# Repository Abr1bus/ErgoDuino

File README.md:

# Ergoduino, an ergo/mech/DIY keyboard

## The project

ErgoDuino is a mechanical keyboard project designed by [Abr1bu5](https://github.com/Abr1bus).

I started to think about it during the first Covid's quarantime, when I was losing my time on [r/MechanicalKeyboard](https://reddit.com/r/MechanicalKeyboards)...

## The tools I used (or will use)

* Layout : [Keyboard Layout Editor](http://www.keyboard-layout-editor.com/)
* Plate : [Plate and Case Builder](http://builder.swillkb.com/)
* Schematics and PCB : [KiCAD](https://kicad.org/)
* Keyboard firmware : [QMK](https://qmk.fm/)

## Where I found all my inspiration/knowledge

* [r/MechanicalKeyboards](https://reddit.com/r/MechanicalKeyboards)
* [r/olkb](https://www.reddit.com/r/olkb/)
* [r/CustomKeyboards](https://www.reddit.com/r/CustomKeyboards/)
* [@Help-14](https://github.com/help-14/mechanical-keyboard) on Github

# Releases

My very first version is on the repo (dev branch), but I don't know if it's working, so if you want to make it, you should check everything !

## Contributing

1. Fork it (<https://github.com/Abr1bus/ErgoDuino>)
2. Create your feature branch `git checkout -b feature/fooBar`
3. Commit your changes `git commit -am 'Add some fooBar'`
4. Push to the branch `git push origin feature/fooBar`
5. Create a new Pull Request

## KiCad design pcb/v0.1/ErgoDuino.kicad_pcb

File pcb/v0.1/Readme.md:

# My KiCAD project

----

Here you will found my KiCAD project, but I have not yet include my libraries.

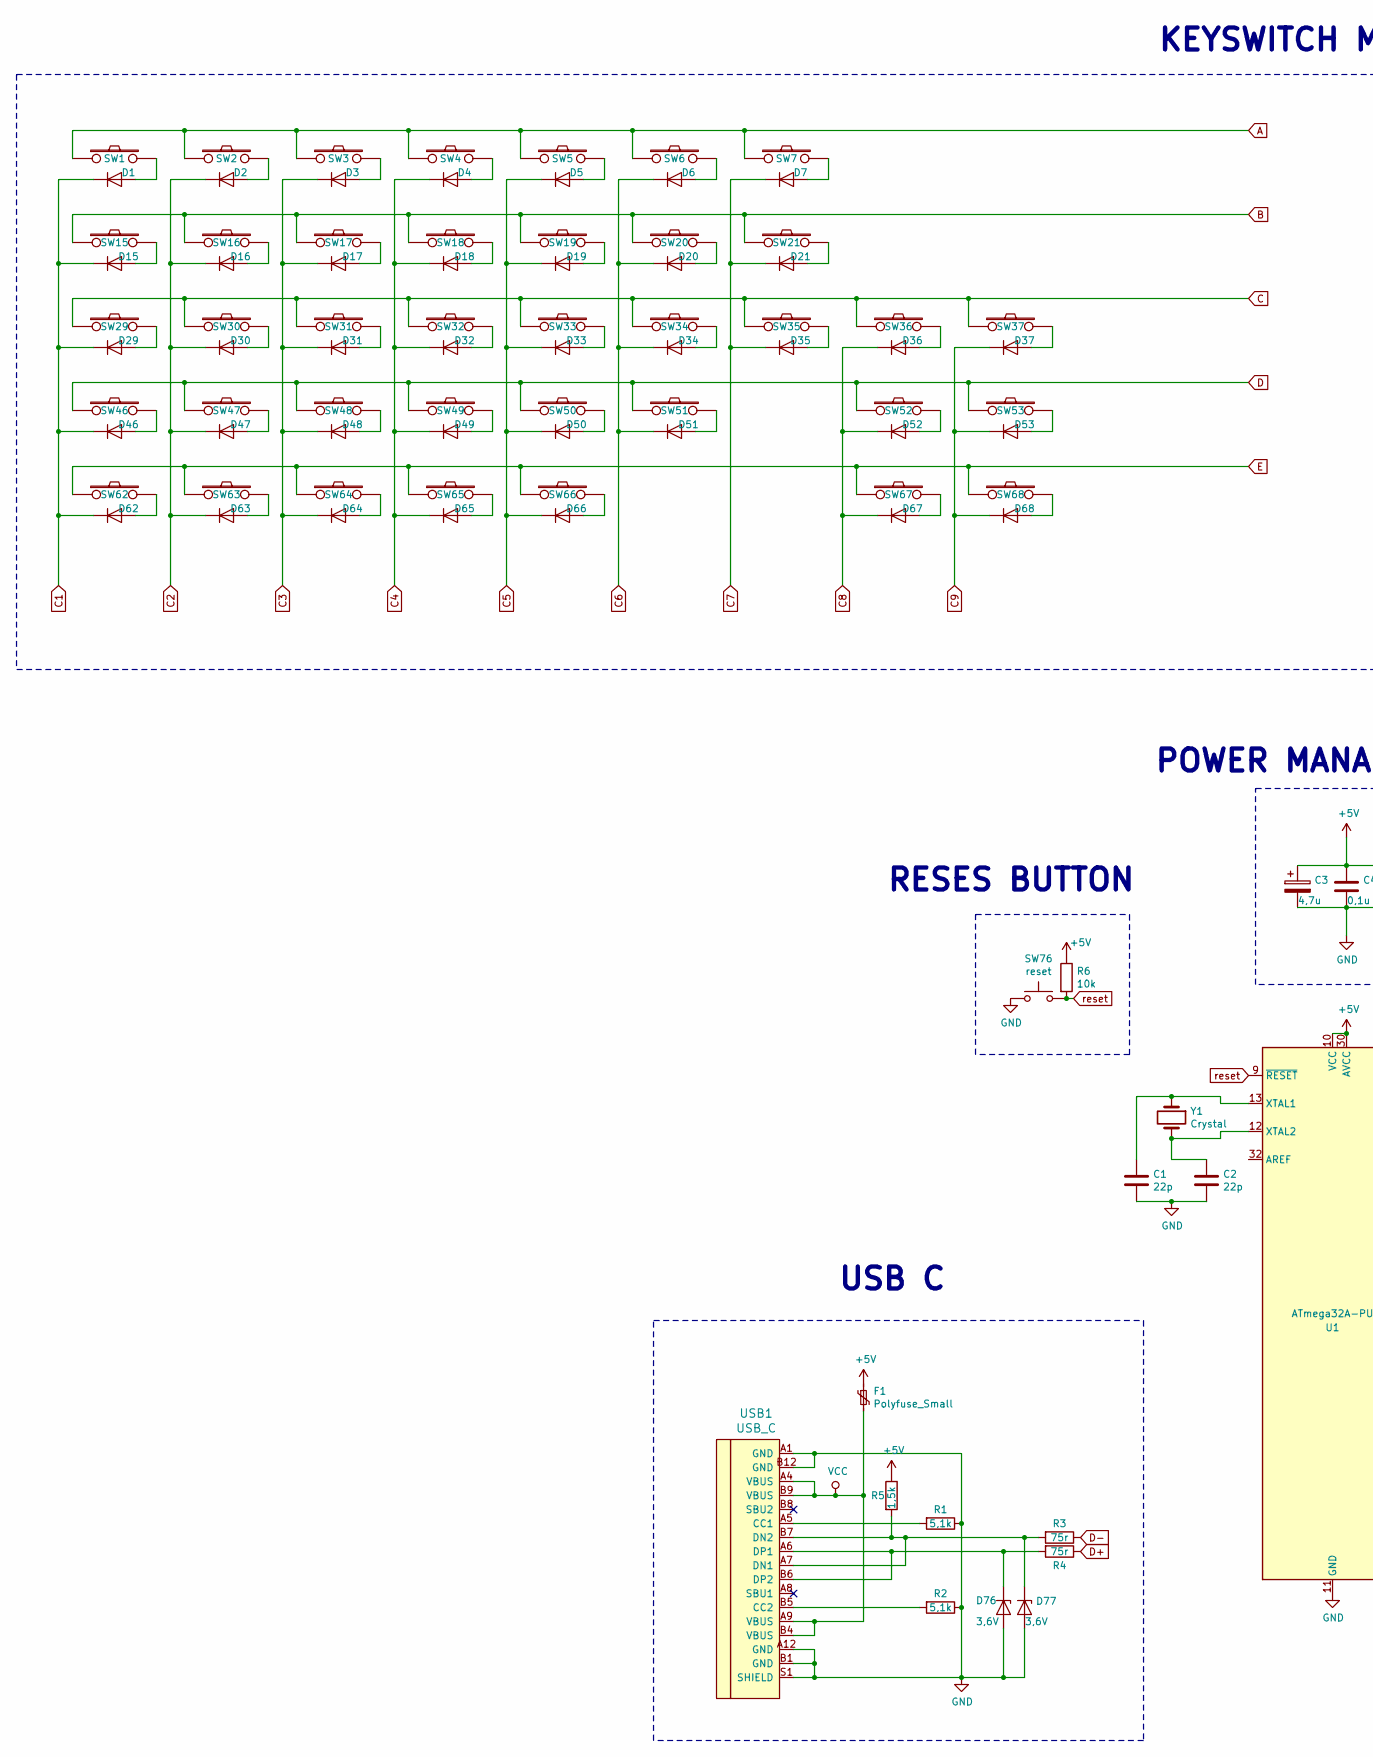
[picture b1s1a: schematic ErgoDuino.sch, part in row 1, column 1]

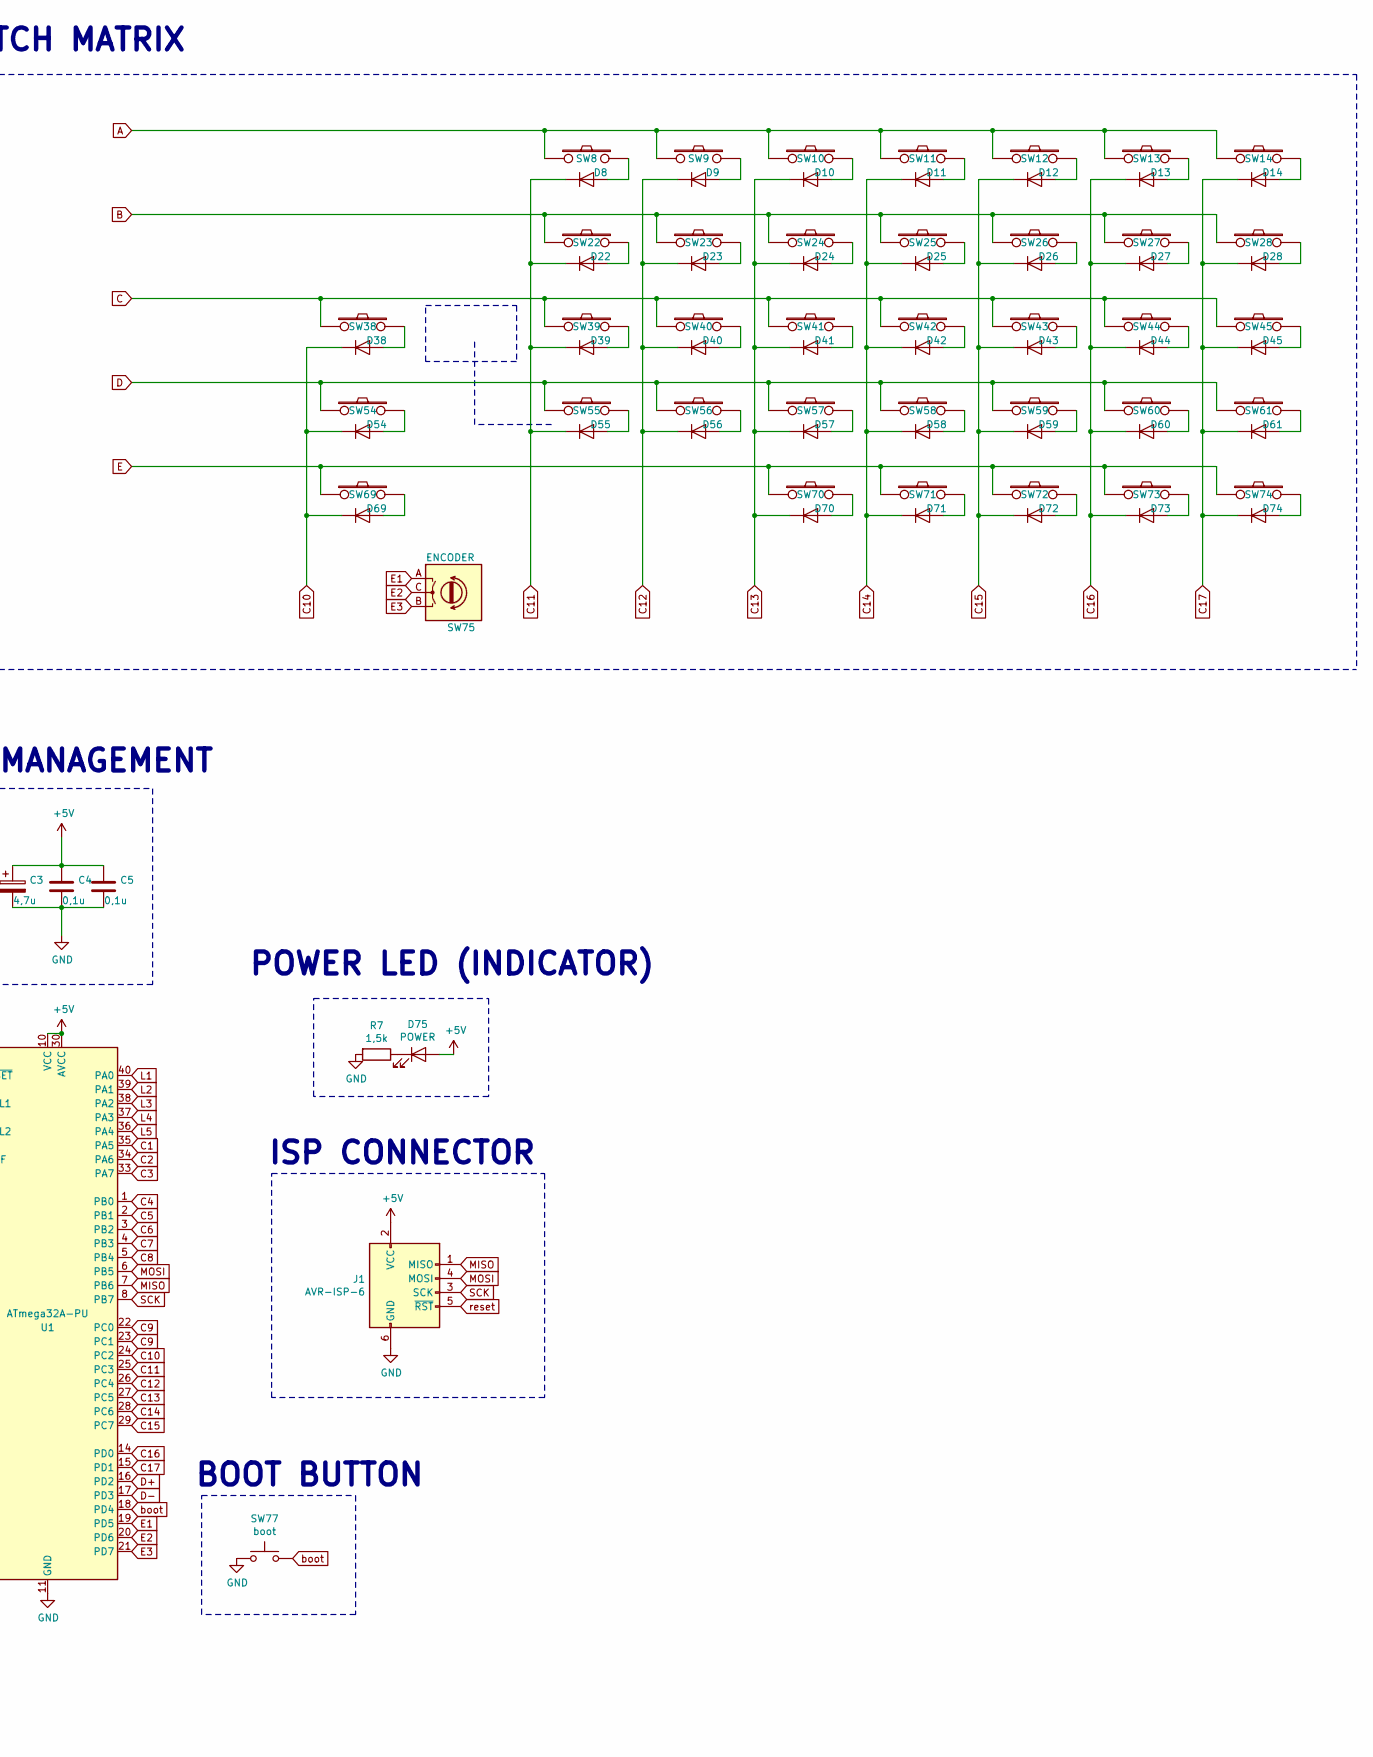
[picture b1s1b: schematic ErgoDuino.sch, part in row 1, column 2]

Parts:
C1, C2: 22p; CP_Radial_D4.0mm_P1.50mm
C3: 4,7u; CP_Radial_D4.0mm_P1.50mm
C4, C5: 0,1u; CP_Radial_D4.0mm_P1.50mm
D1, D2, D3, D4, D5, D6, D7, D8, D9, D10, D11, D12, D13, D14, D15, D16, D17, D18, D19, D20, D21, D22, D23, D24, D25, D26, D27, D28, D29, D30, D31, D32, D33, D34, D35, D36, D37, D38, D39, D40, D41, D42, D43, D44, D45, D46, D47, D48, D49, D50, D51, D52, D53, D54, D55, D56, D57, D58, D59, D60, D61, D62, D63, D64, D65, D66, D67, D68, D69, D70, D71, D72, D73, D74: D; DIODE
D75: POWER; LED_3MM
D76, D77: 3,6V; DIODE
F1: Polyfuse_Small; polyfuse_5.1mm
J1: AVR-ISP-6; AVR_ICSP_3x2
R1, R2: 5,1k; R_Axial_DIN0204_L3.6mm_D1.6mm_P5.08mm_Horizontal
R3, R4: 75r; R_Axial_DIN0204_L3.6mm_D1.6mm_P5.08mm_Horizontal
R5, R7: 1,5k; R_Axial_DIN0204_L3.6mm_D1.6mm_P5.08mm_Horizontal
R6: 10k; R_Axial_DIN0204_L3.6mm_D1.6mm_P5.08mm_Horizontal
SW1, SW14, SW15, SW21, SW22, SW28, SW29, SW35, SW39, SW45, SW46, SW61: SWITCH_PUSH; SW_Cherry_MX_1.50u_PCB
SW2, SW3, SW4, SW5, SW6, SW7, SW8, SW9, SW10, SW11, SW12, SW13, SW16, SW17, SW18, SW19, SW20, SW23, SW24, SW25, SW26, SW27, SW30, SW31, SW32, SW33, SW34, SW36, SW37, SW38, SW40, SW41, SW42, SW43, SW44, SW47, SW48, SW49, SW50, SW51, SW53, SW54, SW55, SW56, SW57, SW58, SW59, SW60, SW62, SW63, SW64, SW65, SW66, SW68, SW69, SW70, SW71, SW72, SW73, SW74: SWITCH_PUSH; SW_Cherry_MX_1.00u_PCB
SW52, SW67: SWITCH_PUSH; SW_Cherry_MX_2.00u_PCB
SW75: ENCODER; RotaryEncoder_Alps_EC11E-Switch_Vertical_H20mm
SW76: reset; SW_PUSH_6mm
SW77: boot; SW_PUSH_6mm
U1: ATmega32A-PU; DIP-40_W15.24mm
USB1: USB_C; USB_C_GCT_USB4085
Y1: Crystal; Crystal_HC49-4H_Vertical

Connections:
+5V: C3.1, C4.1, C5.1, D75.2 (A), F1.1, J1.2 (VCC), R5.1, R6.1, U1.10 (VCC), U1.30 (AVCC)
A: SW1.1, SW2.1, SW3.1, SW4.1, SW5.1, SW6.1, SW7.1, SW8.1, SW9.1, SW10.1, SW11.1, SW12.1, SW13.1, SW14.1
B: SW15.1, SW16.1, SW17.1, SW18.1, SW19.1, SW20.1, SW21.1, SW22.1, SW23.1, SW24.1, SW25.1, SW26.1, SW27.1, SW28.1
C: SW29.1, SW30.1, SW31.1, SW32.1, SW33.1, SW34.1, SW35.1, SW36.1, SW37.1, SW38.1, SW39.1, SW40.1, SW41.1, SW42.1, SW43.1, SW44.1, SW45.1
C1: D1.1 (K), D15.1 (K), D29.1 (K), D46.1 (K), D62.1 (K), U1.35 (PA5)
C2: D2.1 (K), D16.1 (K), D30.1 (K), D47.1 (K), D63.1 (K), U1.34 (PA6)
C3: D3.1 (K), D17.1 (K), D31.1 (K), D48.1 (K), D64.1 (K), U1.33 (PA7)
C4: D4.1 (K), D18.1 (K), D32.1 (K), D49.1 (K), D65.1 (K), U1.1 (PB0)
C5: D5.1 (K), D19.1 (K), D33.1 (K), D50.1 (K), D66.1 (K), U1.2 (PB1)
C6: D6.1 (K), D20.1 (K), D34.1 (K), D51.1 (K), U1.3 (PB2)
C7: D7.1 (K), D21.1 (K), D35.1 (K), U1.4 (PB3)
C8: D36.1 (K), D52.1 (K), D67.1 (K), U1.5 (PB4)
C9: D37.1 (K), D53.1 (K), D68.1 (K), U1.22 (PC0), U1.23 (PC1)
C10: D38.1 (K), D54.1 (K), D69.1 (K), U1.24 (PC2)
C11: D8.1 (K), D22.1 (K), D39.1 (K), D55.1 (K), U1.25 (PC3)
C12: D9.1 (K), D23.1 (K), D40.1 (K), D56.1 (K), U1.26 (PC4)
C13: D10.1 (K), D24.1 (K), D41.1 (K), D57.1 (K), D70.1 (K), U1.27 (PC5)
C14: D11.1 (K), D25.1 (K), D42.1 (K), D58.1 (K), D71.1 (K), U1.28 (PC6)
C15: D12.1 (K), D26.1 (K), D43.1 (K), D59.1 (K), D72.1 (K), U1.29 (PC7)
C16: D13.1 (K), D27.1 (K), D44.1 (K), D60.1 (K), D73.1 (K), U1.14 (PD0)
C17: D14.1 (K), D28.1 (K), D45.1 (K), D61.1 (K), D74.1 (K), U1.15 (PD1)
D: SW46.1, SW47.1, SW48.1, SW49.1, SW50.1, SW51.1, SW52.1, SW53.1, SW54.1, SW55.1, SW56.1, SW57.1, SW58.1, SW59.1, SW60.1, SW61.1
D+: R4.1, U1.16 (PD2)
D-: R3.1, U1.17 (PD3)
E: SW62.1, SW63.1, SW64.1, SW65.1, SW66.1, SW67.1, SW68.1, SW69.1, SW70.1, SW71.1, SW72.1, SW73.1, SW74.1
E1: SW75.A, U1.19 (PD5)
E2: SW75.C, U1.20 (PD6)
E3: SW75.B, U1.21 (PD7)
GND: C1.2, C2.2, C3.2, C4.2, C5.2, D76.2 (A), D77.2 (A), J1.6 (GND), R1.1, R2.1, R7.2, SW76.1, SW77.1, U1.11 (GND), U1.31 (GND), USB1.A1 (GND), USB1.A12 (GND), USB1.B1 (GND), USB1.B12 (GND), USB1.S1 (SHIELD)
L1: U1.40 (PA0)
L2: U1.39 (PA1)
L3: U1.38 (PA2)
L4: U1.37 (PA3)
L5: U1.36 (PA4)
MISO: J1.1 (MISO), U1.7 (PB6)
MOSI: J1.4 (MOSI), U1.6 (PB5)
unnamed: C1.1, U1.13 (XTAL1), Y1.1
unnamed: C2.1, U1.12 (XTAL2), Y1.2
unnamed: D1.2 (A), SW1.2
unnamed: D2.2 (A), SW2.2
unnamed: D3.2 (A), SW3.2
unnamed: D4.2 (A), SW4.2
unnamed: D5.2 (A), SW5.2
unnamed: D6.2 (A), SW6.2
unnamed: D7.2 (A), SW7.2
unnamed: D8.2 (A), SW8.2
unnamed: D9.2 (A), SW9.2
unnamed: D10.2 (A), SW10.2
unnamed: D11.2 (A), SW11.2
unnamed: D12.2 (A), SW12.2
unnamed: D13.2 (A), SW13.2
unnamed: D14.2 (A), SW14.2
unnamed: D15.2 (A), SW15.2
unnamed: D16.2 (A), SW16.2
unnamed: D17.2 (A), SW17.2
unnamed: D18.2 (A), SW18.2
unnamed: D19.2 (A), SW19.2
unnamed: D20.2 (A), SW20.2
unnamed: D21.2 (A), SW21.2
unnamed: D22.2 (A), SW22.2
unnamed: D23.2 (A), SW23.2
unnamed: D24.2 (A), SW24.2
unnamed: D25.2 (A), SW25.2
unnamed: D26.2 (A), SW26.2
unnamed: D27.2 (A), SW27.2
unnamed: D28.2 (A), SW28.2
unnamed: D29.2 (A), SW29.2
unnamed: D30.2 (A), SW30.2
unnamed: D31.2 (A), SW31.2
unnamed: D32.2 (A), SW32.2
unnamed: D33.2 (A), SW33.2
unnamed: D34.2 (A), SW34.2
unnamed: D35.2 (A), SW35.2
unnamed: D36.2 (A), SW36.2
unnamed: D37.2 (A), SW37.2
unnamed: D38.2 (A), SW38.2
unnamed: D39.2 (A), SW39.2
unnamed: D40.2 (A), SW40.2
unnamed: D41.2 (A), SW41.2
unnamed: D42.2 (A), SW42.2
unnamed: D43.2 (A), SW43.2
unnamed: D44.2 (A), SW44.2
unnamed: D45.2 (A), SW45.2
unnamed: D46.2 (A), SW46.2
unnamed: D47.2 (A), SW47.2
unnamed: D48.2 (A), SW48.2
unnamed: D49.2 (A), SW49.2
unnamed: D50.2 (A), SW50.2
unnamed: D51.2 (A), SW51.2
unnamed: D52.2 (A), SW52.2
unnamed: D53.2 (A), SW53.2
unnamed: D54.2 (A), SW54.2
unnamed: D55.2 (A), SW55.2
unnamed: D56.2 (A), SW56.2
unnamed: D57.2 (A), SW57.2
unnamed: D58.2 (A), SW58.2
unnamed: D59.2 (A), SW59.2
unnamed: D60.2 (A), SW60.2
unnamed: D61.2 (A), SW61.2
unnamed: D62.2 (A), SW62.2
unnamed: D63.2 (A), SW63.2
unnamed: D64.2 (A), SW64.2
unnamed: D65.2 (A), SW65.2
unnamed: D66.2 (A), SW66.2
unnamed: D67.2 (A), SW67.2
unnamed: D68.2 (A), SW68.2
unnamed: D69.2 (A), SW69.2
unnamed: D70.2 (A), SW70.2
unnamed: D71.2 (A), SW71.2
unnamed: D72.2 (A), SW72.2
unnamed: D73.2 (A), SW73.2
unnamed: D74.2 (A), SW74.2
unnamed: D75.1 (K), R7.1
unnamed: D76.1 (K), R4.2, USB1.A6 (DP1), USB1.B6 (DP2)
unnamed: D77.1 (K), R3.2, R5.2, USB1.A7 (DN1), USB1.B7 (DN2)
unnamed: R1.2, USB1.A5 (CC1)
unnamed: R2.2, USB1.B5 (CC2)
SCK: J1.3 (SCK), U1.8 (PB7)
VCC: F1.2, USB1.A4 (VBUS), USB1.A9 (VBUS), USB1.B4 (VBUS), USB1.B9 (VBUS)
boot: SW77.2, U1.18 (PD4)
reset: J1.5 (~RST), R6.2, SW76.2, U1.9 (~RESET)

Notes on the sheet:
USB C
RESES BUTTON
POWER MANAGEMENT
POWER LED (INDICATOR)
ISP CONNECTOR
BOOT BUTTON
KEYSWITCH MATRIX

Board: 2 copper layers, 171 parts (0 on the bottom side), 116 nets, no tracks yet.

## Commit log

2021-04-26 Upload my project
2021-04-27 Update shields
2021-04-27 Update Readme (again)
2021-04-27 Again...
2021-04-27 Add banner
2021-04-27 Update issue templates
